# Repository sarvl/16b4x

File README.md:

## Under Construction 

## Documentation
Most up to date documentation and specification can be found in `documentation/`  
see

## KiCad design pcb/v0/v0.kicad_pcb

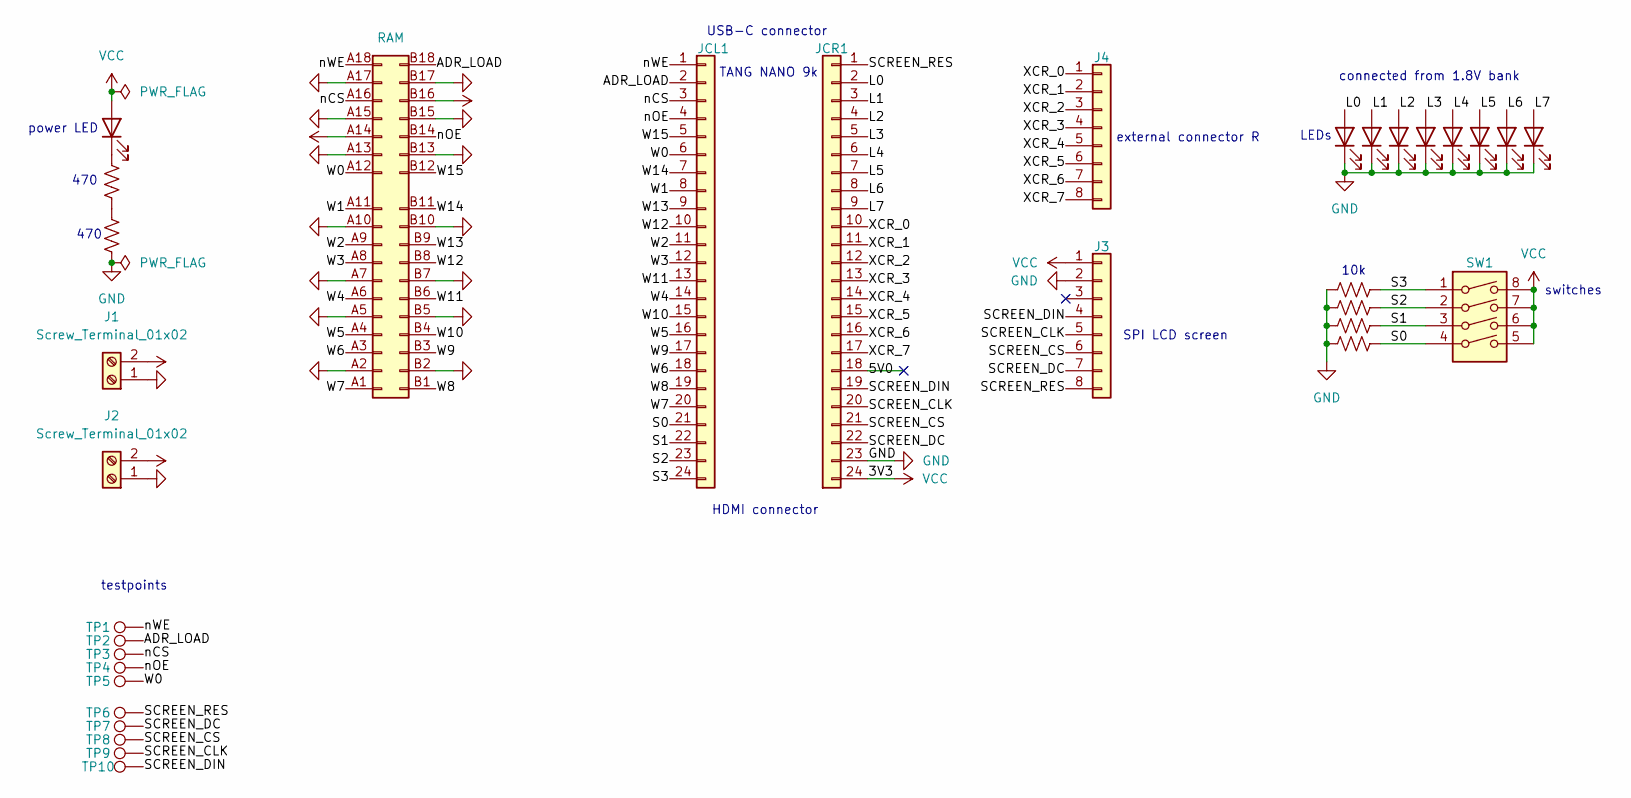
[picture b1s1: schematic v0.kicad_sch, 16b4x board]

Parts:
D0, D1, D2, D3, D4, D5, D6, D7: WHITE; LED_0603_1608Metric
DP1: GREEN; LED_0603_1608Metric
J1, J2: Screw_Terminal_01x02; TerminalBlock_Phoenix_MPT-0,5-2-2.54_1x02_P2.54mm_Horizontal
J3, J4: Conn_01x08; PinSocket_1x08_P2.54mm_Vertical
J6: RAM; CONN-TH_X3183WV-36B1-46V15
JCL1: Conn_01x24; PinSocket_1x24_P2.54mm_Vertical
JCR1: Conn_01x24; PinSocket_1x24_P2.54mm_Vertical
R1, R6: 470; R_0402_1005Metric
R2, R3, R4, R5: 10k; R_0603_1608Metric
SW1: SW_DIP_x04; SW_DIP_SPSTx04_Slide_9.78x12.34mm_W7.62mm_P2.54mm
TP1, TP2, TP3, TP4, TP5, TP6, TP7, TP8, TP9, TP10: TestPoint; TestPoint_Pad_D1.0mm

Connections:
/5V0: JCR1.18
/ADR_LOAD: J6.B18, JCL1.2, TP2.1 (1_1)
/L0: D0.2 (A), JCR1.2
/L1: D1.2 (A), JCR1.3
/L2: D2.2 (A), JCR1.4
/L3: D3.2 (A), JCR1.5
/L4: D4.2 (A), JCR1.6
/L5: D5.2 (A), JCR1.7
/L6: D6.2 (A), JCR1.8
/L7: D7.2 (A), JCR1.9
/S0: JCL1.21, R5.2, SW1.4
/S1: JCL1.22, R4.2, SW1.3
/S2: JCL1.23, R3.2, SW1.2
/S3: JCL1.24, R2.2, SW1.1
/SCREEN_CLK: J3.5, JCR1.20, TP9.1 (1_1)
/SCREEN_CS: J3.6, JCR1.21, TP8.1 (1_1)
/SCREEN_DC: J3.7, JCR1.22, TP7.1 (1_1)
/SCREEN_DIN: J3.4, JCR1.19, TP10.1 (1_1)
/SCREEN_RES: J3.8, JCR1.1, TP6.1 (1_1)
/W0: J6.A12, JCL1.6, TP5.1 (1_1)
/W1: J6.A11, JCL1.8
/W2: J6.A9, JCL1.11
/W3: J6.A8, JCL1.12
/W4: J6.A6, JCL1.14
/W5: J6.A4, JCL1.16
/W6: J6.A3, JCL1.18
/W7: J6.A1, JCL1.20
/W8: J6.B1, JCL1.19
/W9: J6.B3, JCL1.17
/W10: J6.B4, JCL1.15
/W11: J6.B6, JCL1.13
/W12: J6.B8, JCL1.10
/W13: J6.B9, JCL1.9
/W14: J6.B11, JCL1.7
/W15: J6.B12, JCL1.5
/XCR_0: J4.1, JCR1.10
/XCR_1: J4.2, JCR1.11
/XCR_2: J4.3, JCR1.12
/XCR_3: J4.4, JCR1.13
/XCR_4: J4.5, JCR1.14
/XCR_5: J4.6, JCR1.15
/XCR_6: J4.7, JCR1.16
/XCR_7: J4.8, JCR1.17
/nCS: J6.A16, JCL1.3, TP3.1 (1_1)
/nOE: J6.B14, JCL1.4, TP4.1 (1_1)
/nWE: J6.A18, JCL1.1, TP1.1 (1_1)
GND: D0.1 (K), D1.1 (K), D2.1 (K), D3.1 (K), D4.1 (K), D5.1 (K), D6.1 (K), D7.1 (K), J1.1, J2.1, J3.2, J6.A2, J6.A5, J6.A7, J6.A10, J6.A13, J6.A15, J6.A17, J6.B2, J6.B5, J6.B7, J6.B10, J6.B13, J6.B15, J6.B17, JCR1.23, R2.1, R3.1, R4.1, R5.1, R6.1
unnamed: DP1.1 (K), R1.2
unnamed: R1.1, R6.2
VCC: DP1.2 (A), J1.2, J2.2, J3.1, J6.A14, J6.B16, JCR1.24, SW1.5, SW1.6, SW1.7, SW1.8

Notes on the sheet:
connected from 1.8V bank
external connector R
TANG NANO 9k
HDMI connector
LEDs
power LED
SPI LCD screen
470
USB-C connector
testpoints
10k
switches

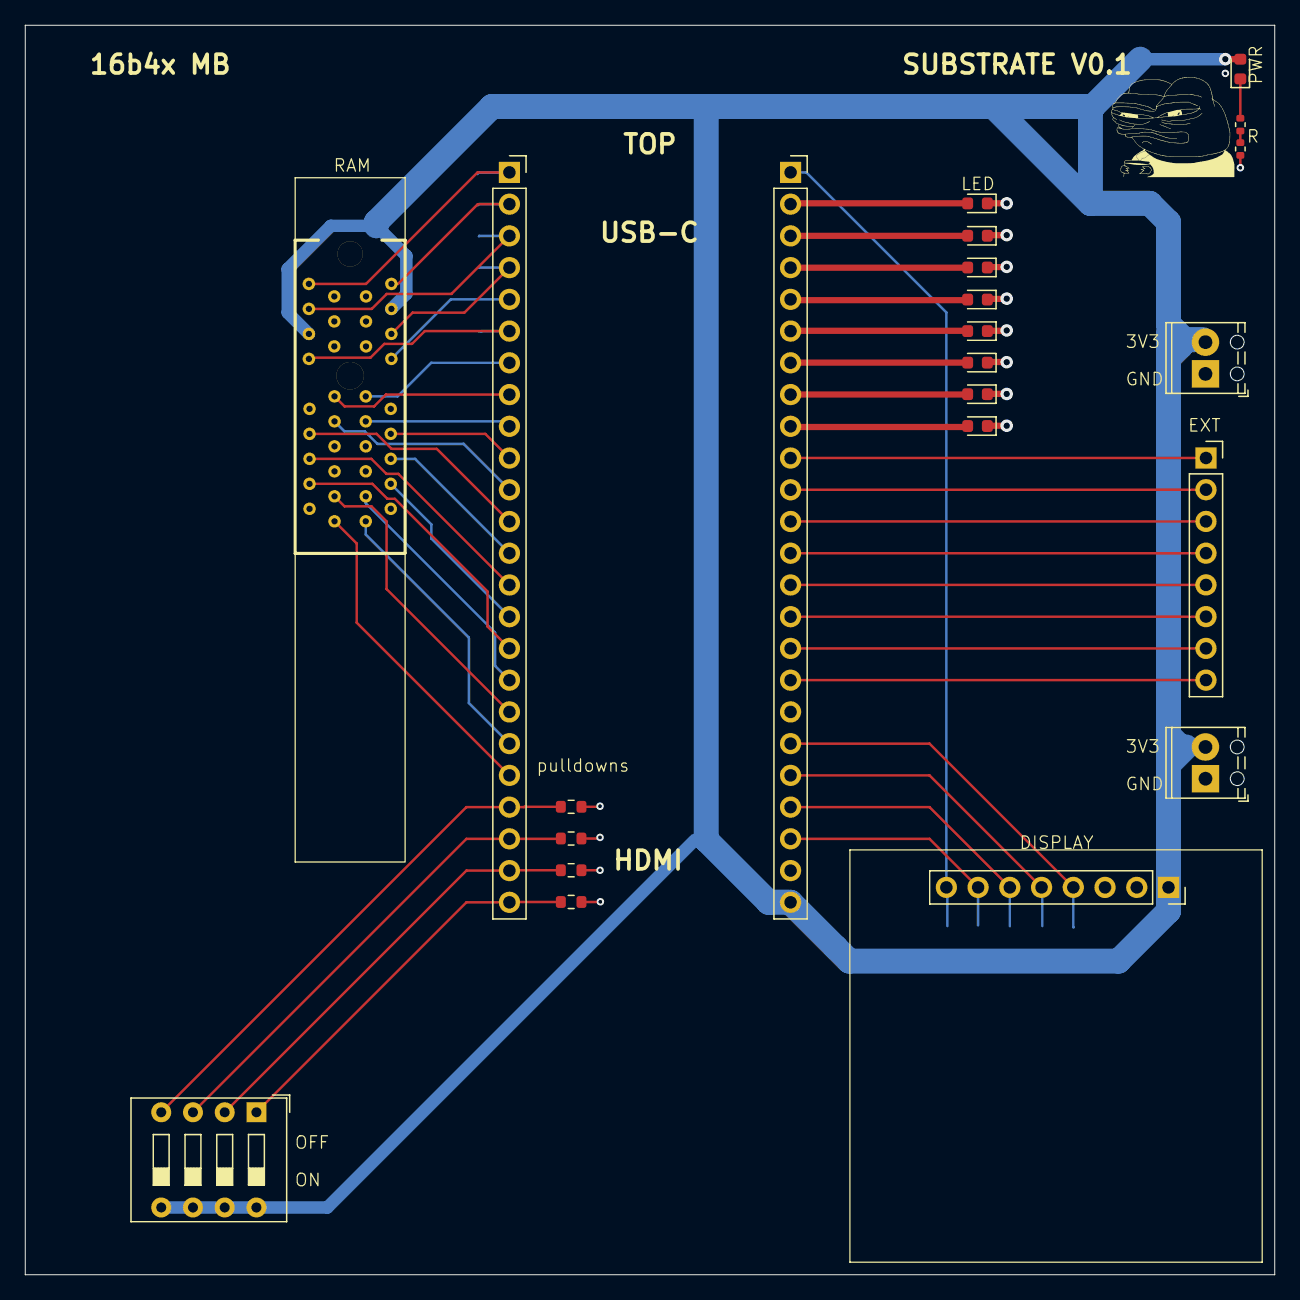
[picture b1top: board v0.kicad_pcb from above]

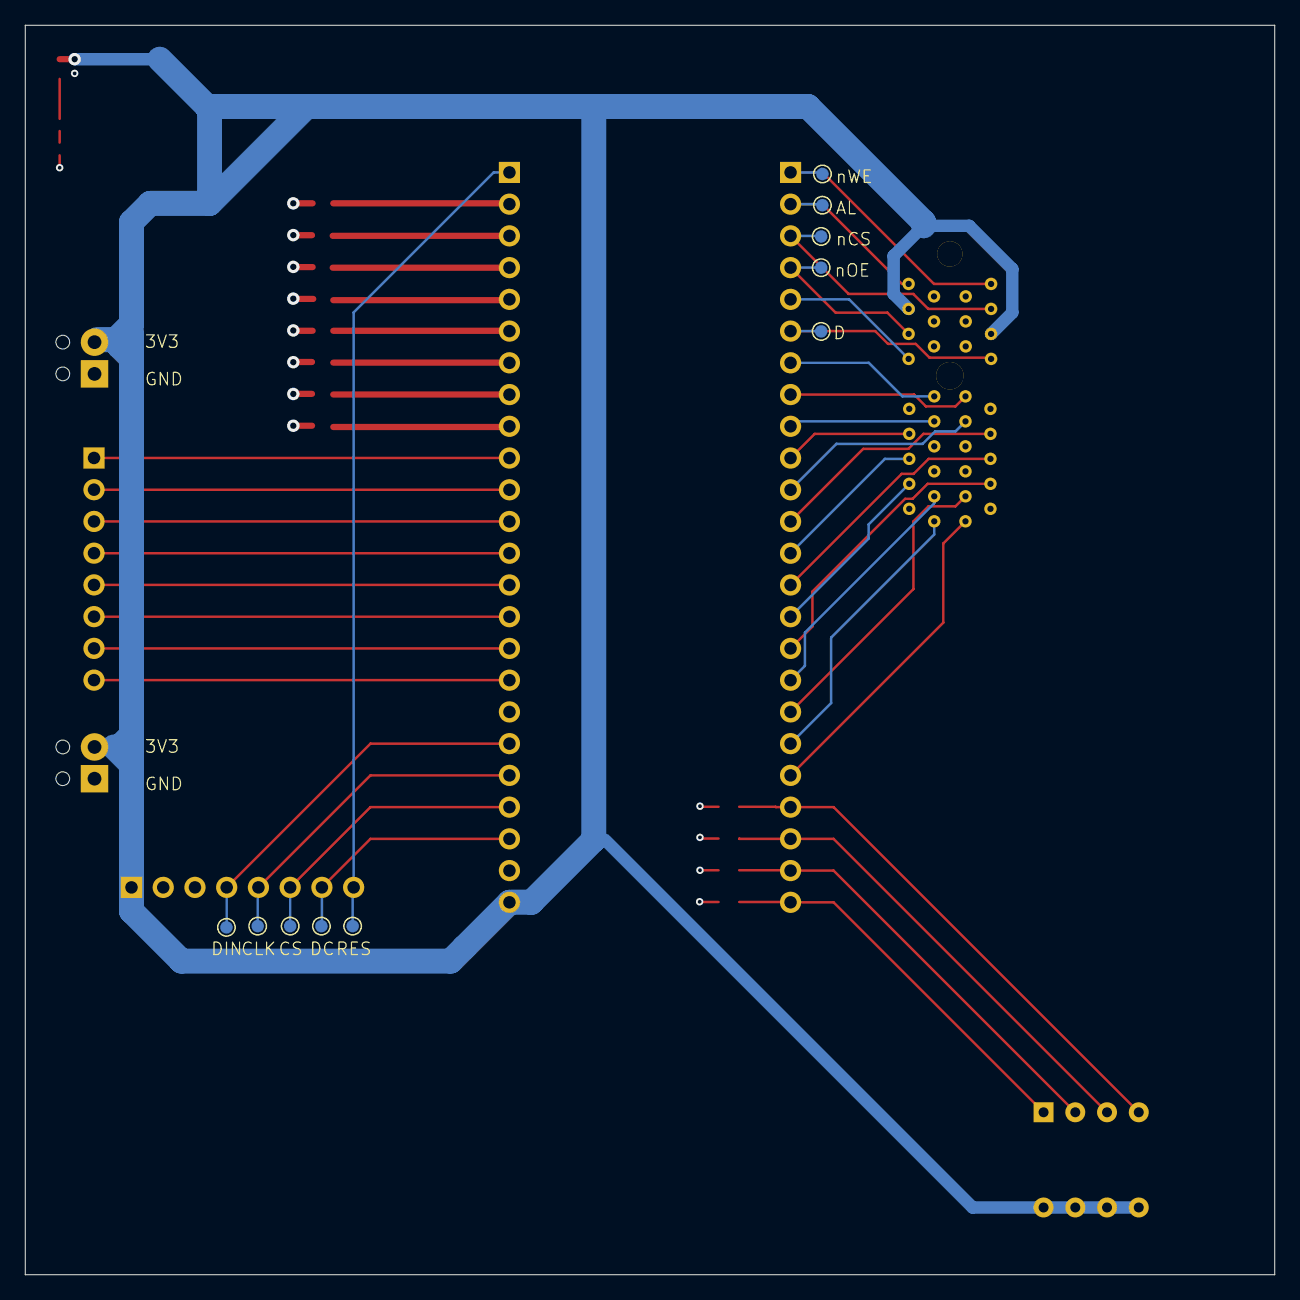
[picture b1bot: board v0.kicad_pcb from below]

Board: 4 copper layers, 100.0 x 100.0 mm, 33 parts (10 on the bottom side), 49 nets.

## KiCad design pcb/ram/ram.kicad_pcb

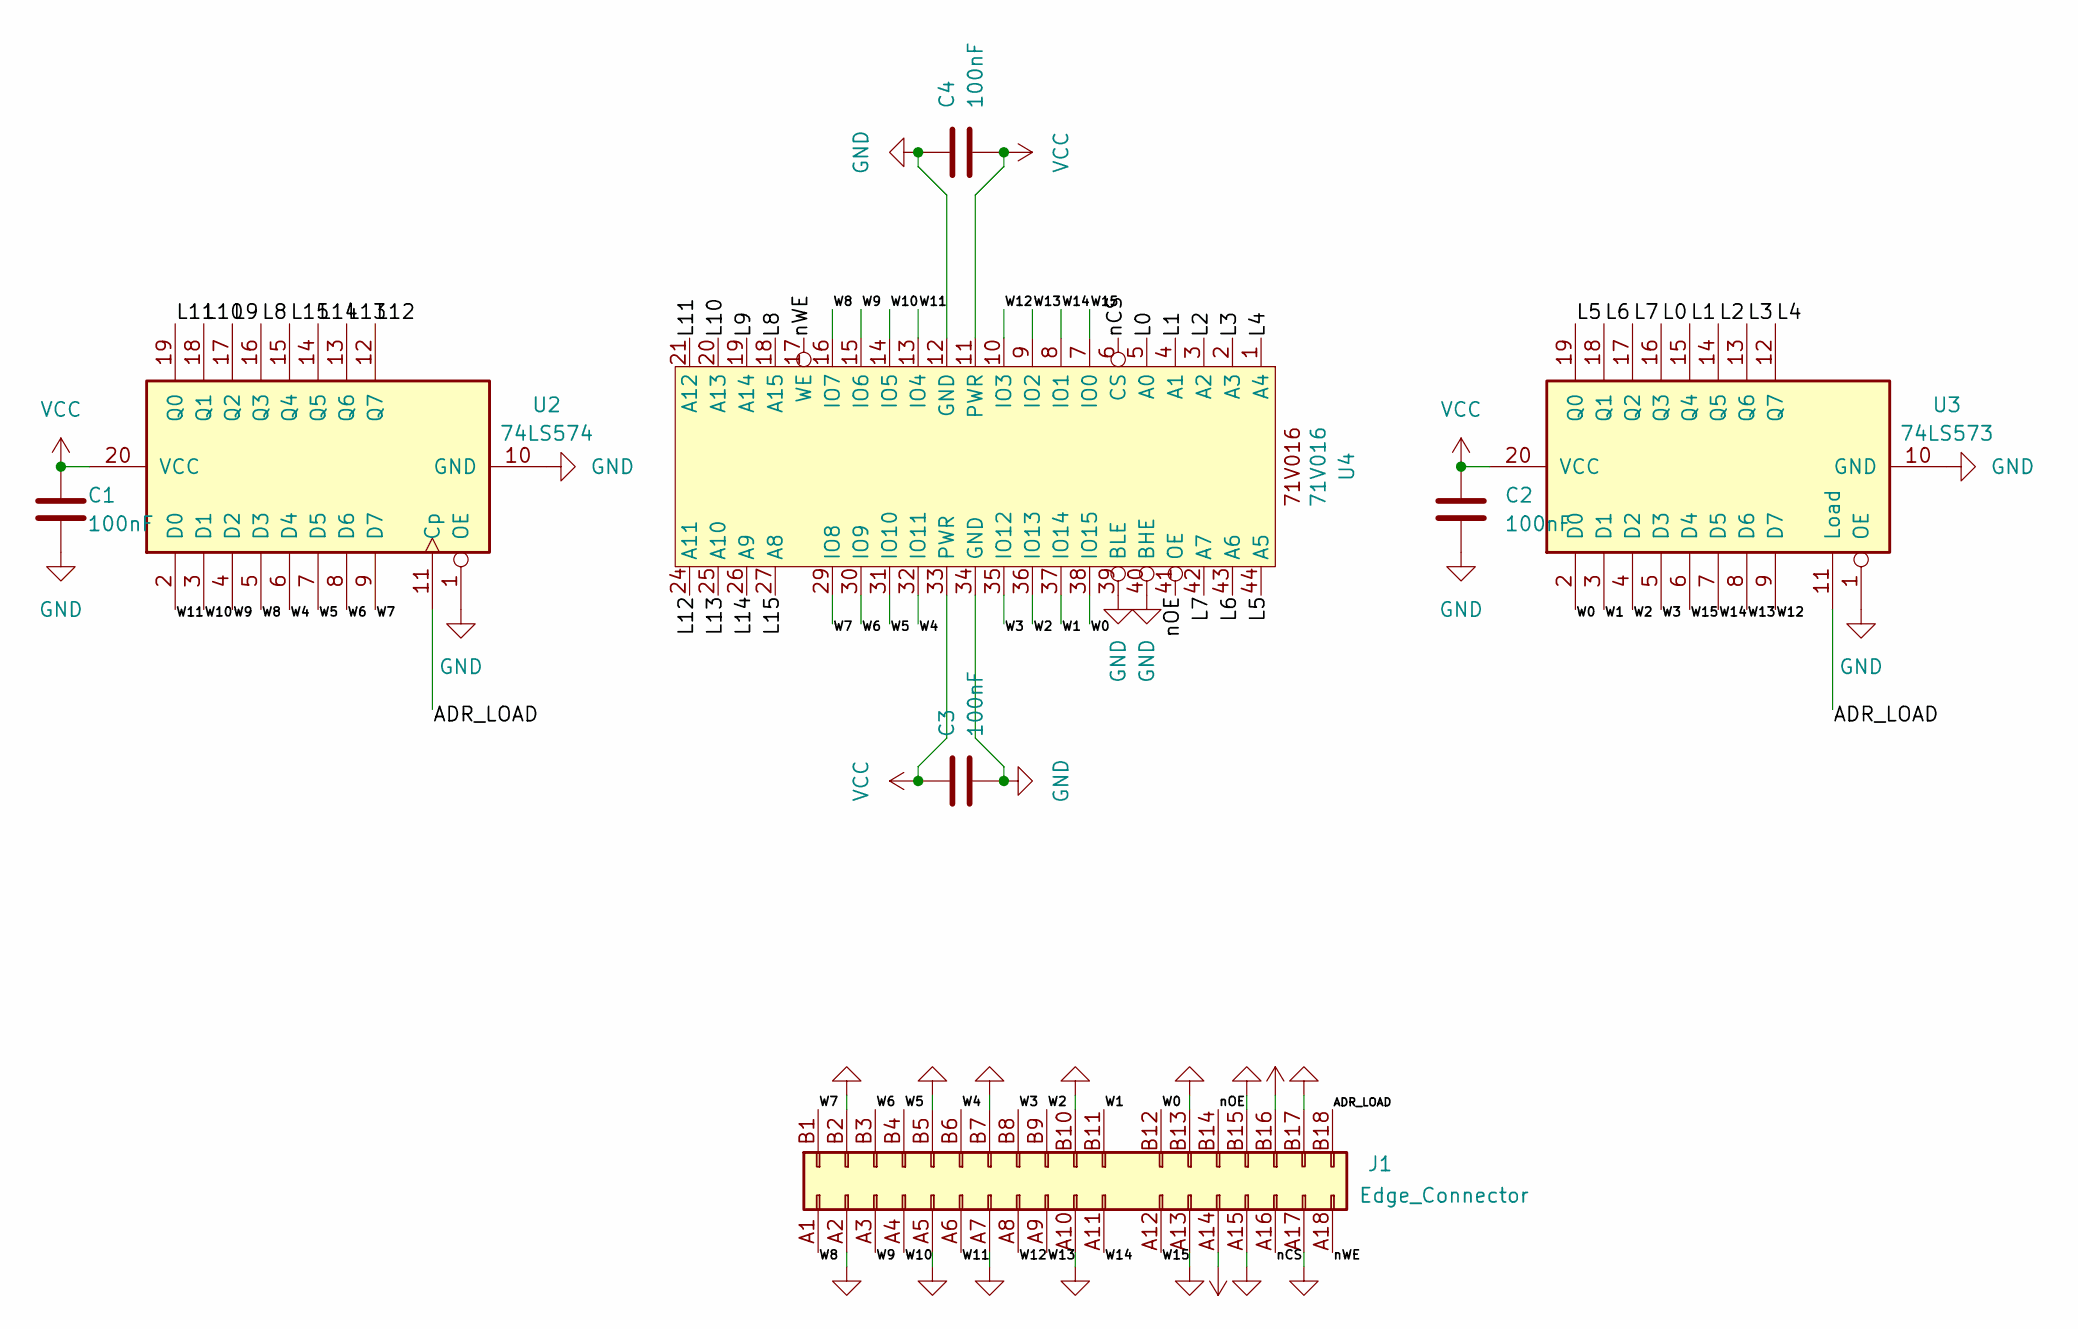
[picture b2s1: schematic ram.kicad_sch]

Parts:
C1, C2, C3, C4: 100nF; C_0603_1608Metric
J1: Edge_Connector; BUS_PCIexpress_x1
U2: 74LS574; SOIC-20W_7.5x12.8mm_P1.27mm
U3: 74LS573; SOIC-20W_7.5x12.8mm_P1.27mm
U4: 71V016; TSOP-II-44_10.16x18.41mm_P0.8mm

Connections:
/ADR_LOAD: J1.B18, U2.11 (Cp), U3.11 (Load)
/L0: U3.16 (Q3), U4.5 (A0)
/L1: U3.15 (Q4), U4.4 (A1)
/L2: U3.14 (Q5), U4.3 (A2)
/L3: U3.13 (Q6), U4.2 (A3)
/L4: U3.12 (Q7), U4.1 (A4)
/L5: U3.19 (Q0), U4.44 (A5)
/L6: U3.18 (Q1), U4.43 (A6)
/L7: U3.17 (Q2), U4.42 (A7)
/L8: U2.16 (Q3), U4.18 (A15)
/L9: U2.17 (Q2), U4.19 (A14)
/L10: U2.18 (Q1), U4.20 (A13)
/L11: U2.19 (Q0), U4.21 (A12)
/L12: U2.12 (Q7), U4.24 (A11)
/L13: U2.13 (Q6), U4.25 (A10)
/L14: U2.14 (Q5), U4.26 (A9)
/L15: U2.15 (Q4), U4.27 (A8)
/W0: J1.B12, U3.2 (D0), U4.38 (IO15)
/W1: J1.B11, U3.3 (D1), U4.37 (IO14)
/W2: J1.B9, U3.4 (D2), U4.36 (IO13)
/W3: J1.B8, U3.5 (D3), U4.35 (IO12)
/W4: J1.B6, U2.6 (D4), U4.32 (IO11)
/W5: J1.B4, U2.7 (D5), U4.31 (IO10)
/W6: J1.B3, U2.8 (D6), U4.30 (IO9)
/W7: J1.B1 (B2), U2.9 (D7), U4.29 (IO8)
/W8: J1.A1, U2.5 (D3), U4.16 (IO7)
/W9: J1.A3, U2.4 (D2), U4.15 (IO6)
/W10: J1.A4, U2.3 (D1), U4.14 (IO5)
/W11: J1.A6, U2.2 (D0), U4.13 (IO4)
/W12: J1.A8, U3.9 (D7), U4.10 (IO3)
/W13: J1.A9, U3.8 (D6), U4.9 (IO2)
/W14: J1.A11, U3.7 (D5), U4.8 (IO1)
/W15: J1.A12, U3.6 (D4), U4.7 (IO0)
/nCS: J1.A16, U4.6 (CS)
/nOE: J1.B14, U4.41 (OE)
/nWE: J1.A18, U4.17 (WE)
GND: C1.2, C2.2, C3.2, C4.1, J1.A2, J1.A5, J1.A7, J1.A10, J1.A13, J1.A15, J1.A17, J1.B2, J1.B5, J1.B7, J1.B10, J1.B13, J1.B15, J1.B17, U2.1 (OE), U2.10 (GND), U3.1 (OE), U3.10 (GND), U4.12 (GND), U4.34 (GND), U4.39 (BLE), U4.40 (BHE)
VCC: C1.1, C2.1, C3.1, C4.2, J1.A14, J1.B16, U2.20 (VCC), U3.20 (VCC), U4.11 (PWR), U4.33 (PWR)

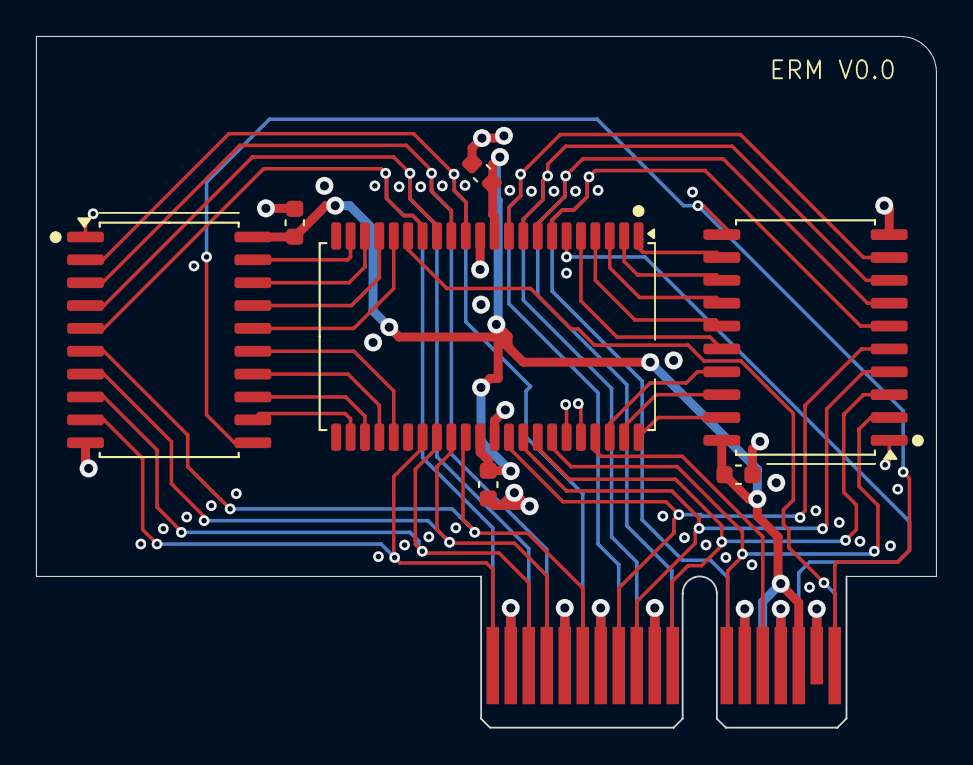
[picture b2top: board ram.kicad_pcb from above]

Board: 4 copper layers, 50.0 x 38.4 mm, 8 parts (0 on the bottom side), 38 nets.

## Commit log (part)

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2024-07-07 fpga first draft
2024-07-18 primitive OS ; VM first draft
2024-08-04 helium implementation ; VM ; mem and flash controller
2024-08-16 assembler rewrite ; directives ; expressions ; format output ; docs ; test system ; interface ; warning control ; syntax highlight ; labels improvement ; minor fixes/features
2024-08-16 type fixes ; interactive mode for dasm
2024-08-25 PCBs
2024-08-28 ISA & tooling update - perf counters, istructions, IO
2024-08-29 test of linguist for .sasm extension
